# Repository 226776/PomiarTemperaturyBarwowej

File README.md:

# Pomiar Temperatury Barwowej
Repozytorium zawiera wszystkie niezbędne elementy projektu, najważniejsze z nich wymieniono poniżej:
- Katalog Hardware:
	- projekt płytki wykonany w środowisku eagle 
	- pining 
- Katalog pdf:
	- pdf płytką w skali 1:1  
	- pdf zawierający schemat układu akwizycji danych
- Katalog Scripts: 
	- skrypt wyliczający model
	- skrypt obsługujący pomiar temperatury barwowej
- Katalog MCU_Software:
	- pliki oprogramowania mikrokontrolera w tym plik main 
- Katalog Measurements 
	- pomiary źródeł światła
	- skrypty jupyter notebook

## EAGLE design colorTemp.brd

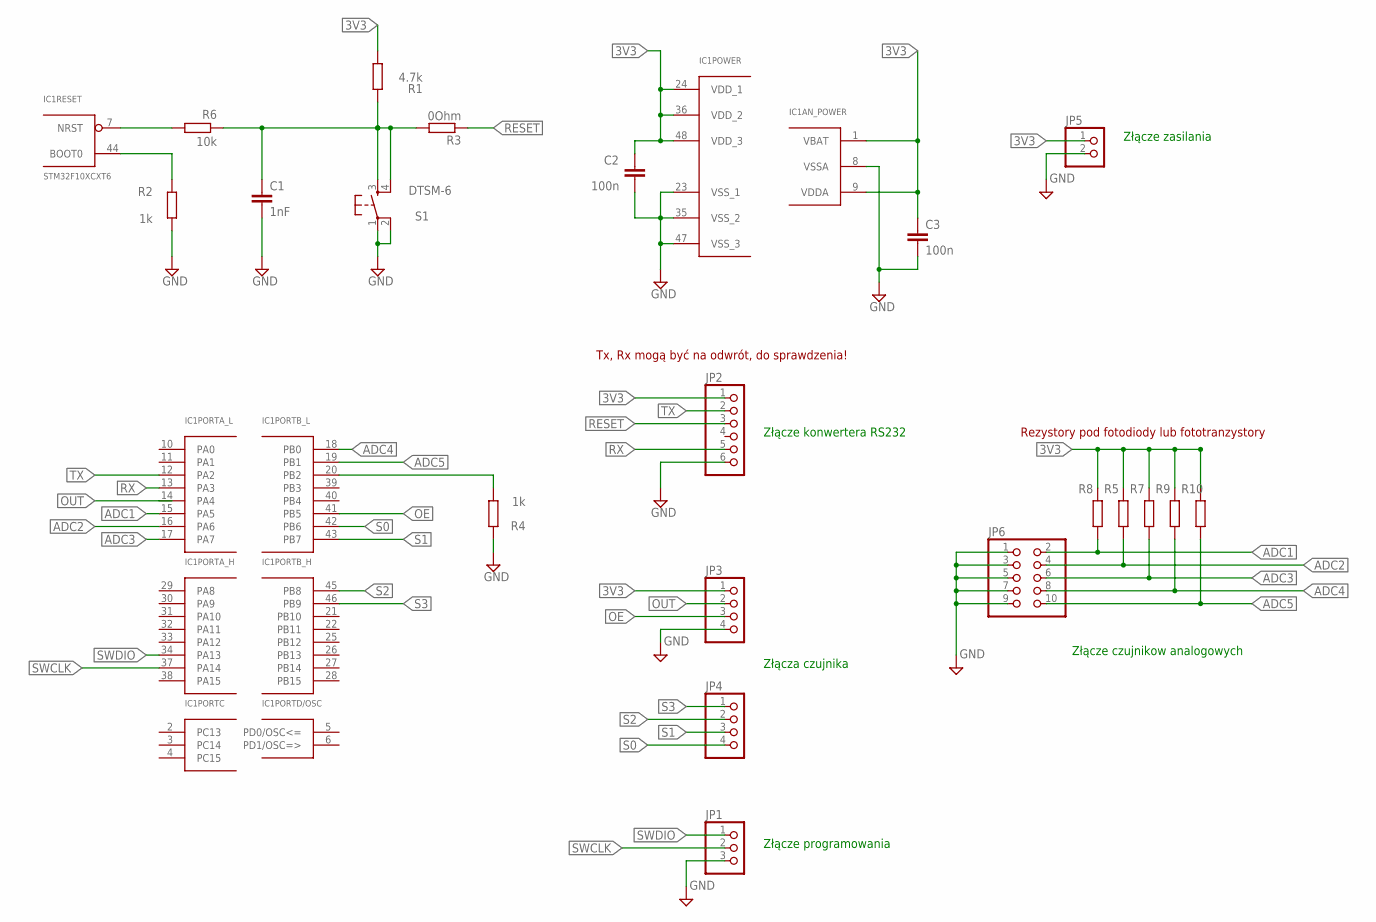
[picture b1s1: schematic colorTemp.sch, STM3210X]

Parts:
C1: 1nF; C0402
C2, C3: 100n; C0402
IC1: STM32F10XCXT6; TQFP48
JP1: PINHD-1X3; 1X03
JP2: PINHD-1X6/90; 1X06/90
JP3, JP4: PINHD-1X4; 1X04
JP5: PINHD-1X2; 1X02
JP6: PINHD-2X5; 2X05
R1: 4.7k; R0402
R2, R4: 1k; R0402
R3: 0Ohm; R0402
R5, R7, R8, R9, R10: R-EU_R0402; R0402
R6: 10k; R0402
S1: DTSM-6

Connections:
3V3: C2.1, C3.1, IC1.1 (VBAT), IC1.9 (VDDA), IC1.24 (VDD_1), IC1.36 (VDD_2), IC1.48 (VDD_3), JP2.1, JP3.1, JP5.1, R1.2, R5.1, R7.1, R8.1, R9.1, R10.1
ADC1: IC1.15 (PA5), JP6.2, R8.2
ADC2: IC1.16 (PA6), JP6.4, R5.2
ADC3: IC1.17 (PA7), JP6.6, R7.2
ADC4: IC1.18 (PB0), JP6.8, R9.2
ADC5: IC1.19 (PB1), JP6.10, R10.2
GND: C1.2, C2.2, C3.2, IC1.8 (VSSA), IC1.23 (VSS_1), IC1.35 (VSS_2), IC1.47 (VSS_3), JP1.3, JP2.6, JP3.4, JP5.2, JP6.1, JP6.3, JP6.5, JP6.7, JP6.9, R2.1, R4.1, S1.1, S1.2
unnamed: IC1.44 (BOOT0), R2.2
unnamed: IC1.20 (PB2), R4.2
unnamed: IC1.7 (NRST), R6.2
unnamed: C1.1, R1.1, R3.2, R6.1, S1.3, S1.4
OE: IC1.41 (PB5), JP3.3
OUT: IC1.14 (PA4), JP3.2
RESET: JP2.3, R3.1
RX: IC1.13 (PA3), JP2.5
S0: IC1.42 (PB6), JP4.4
S1: IC1.43 (PB7), JP4.3
S2: IC1.45 (PB8), JP4.2
S3: IC1.46 (PB9), JP4.1
SWCLK: IC1.37 (PA14), JP1.2
SWDIO: IC1.34 (PA13), JP1.1
TX: IC1.12 (PA2), JP2.2

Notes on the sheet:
Tx, Rx mogą być na odwrót, do sprawdzenia!
Złącze konwertera RS232
Złącza czujnika
Złącze programowania
Złącze zasilania
Złącze czujnikow analogowych
Rezystory pod fotodiody lub fototranzystory

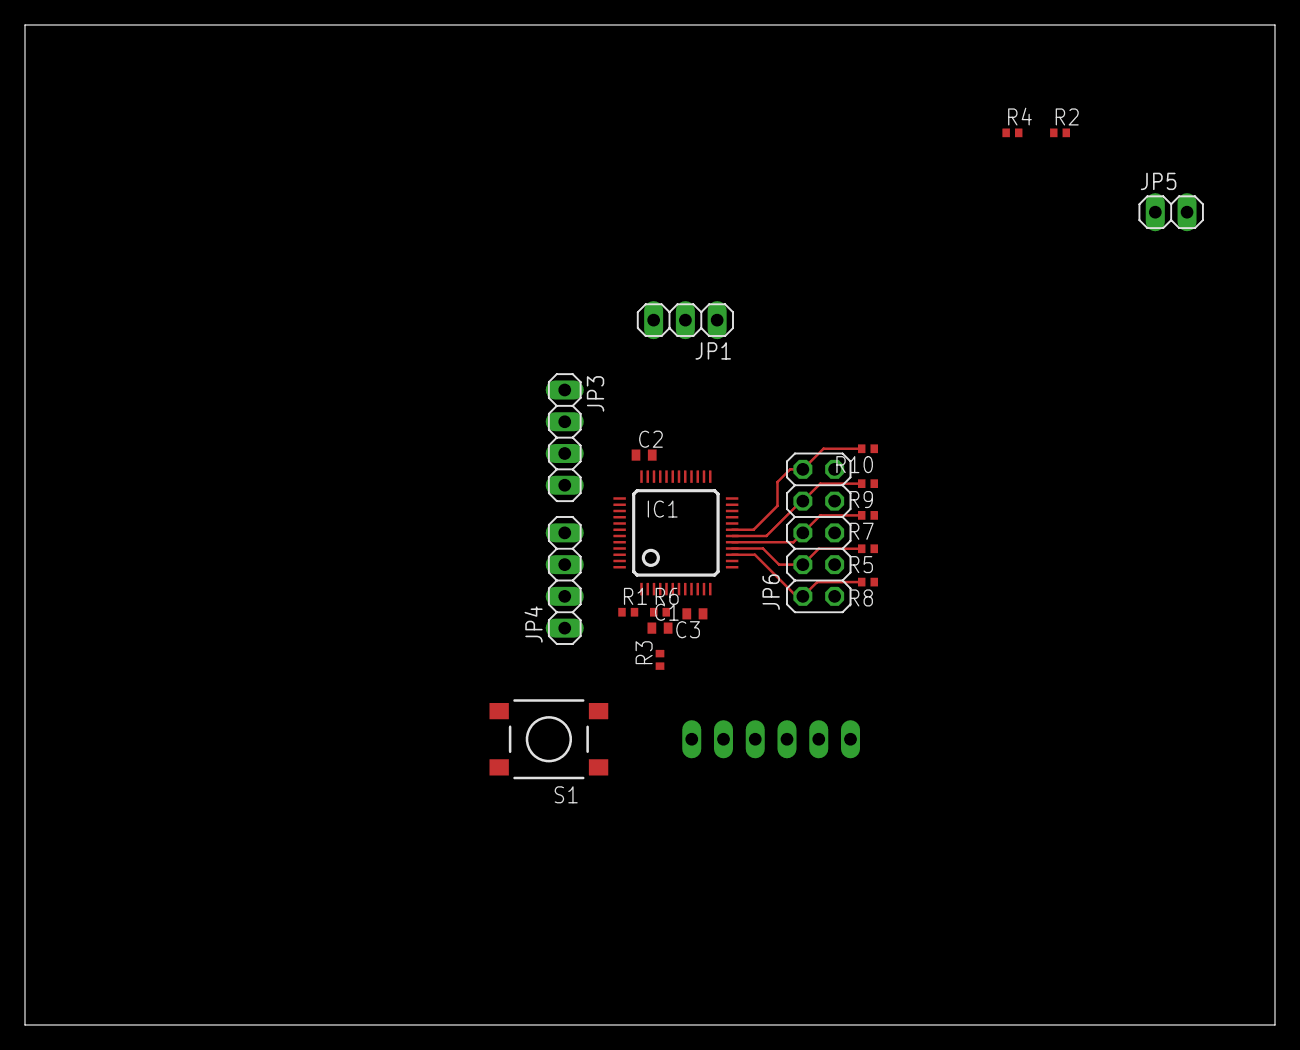
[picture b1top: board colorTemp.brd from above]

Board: 2 copper layers, 100.0 x 80.0 mm, 21 parts (1 on the bottom side), 22 nets.

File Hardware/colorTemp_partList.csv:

"Qty";"Value";"Device";"Package";"Parts";"Description";"SPICEPREFIX";
"1";"";"PINHD-1X2";"1X02";"JP5";"PIN HEADER";"";
"1";"";"PINHD-1X3";"1X03";"JP1";"PIN HEADER";"";
"2";"";"PINHD-1X4";"1X04";"JP3, JP4";"PIN HEADER";"";
"1";"";"PINHD-1X6/90";"1X06/90";"JP2";"PIN HEADER";"";
"1";"";"PINHD-2X5";"2X05";"JP6";"PIN HEADER";"";
"5";"";"R-EU_R0402";"R0402";"R5, R7, R8, R9, R10";"RESISTOR, European symbol";"R";
"1";"0Ohm";"R-EU_R0402";"R0402";"R3";"RESISTOR, European symbol";"R";
"2";"100n";"C-EUC0402";"C0402";"C2, C3";"CAPACITOR, European symbol";"C";
"1";"10k";"R-EU_R0402";"R0402";"R6";"RESISTOR, European symbol";"R";
"2";"1k";"R-EU_R0402";"R0402";"R2, R4";"RESISTOR, European symbol";"R";
"1";"1nF";"C-EUC0402";"C0402";"C1";"CAPACITOR, European symbol";"C";
"1";"4.7k";"R-EU_R0402";"R0402";"R1";"RESISTOR, European symbol";"R";
"1";"DTSM-6";"DTSM-6";"DTSM-6";"S1";"";"";
"1";"STM32F10XCXT6";"STM32F10XCXT6";"TQFP48";"IC1";"ST STM32F101/103 48pin LQFP";"";

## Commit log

2020-03-30 Pinning
2020-03-30 Cleanup
2020-04-05 Power supply schematic
2020-04-05 Schematic STM3210X section
2020-04-05 TCS3200 datasheet add
2020-04-05 Schematic pdf
2020-04-05 Supply change
2020-04-05 Schematic Update
2020-04-18 Board in progress
2020-04-18 Board update
2020-05-17 Images Upload
2020-05-17 Added new comments to the main.c file
2020-05-17 Added new comments in main.c file
2020-05-17 Images Rename
2020-05-18 Project CleanUp
2020-05-31 mesuing patterns
2020-05-31 Algorytm programu MCU
2020-05-31 Block Diagram add
2020-06-02 Measure via serial python script in progress
2020-06-07 BoardView.png upload
2020-06-07 Creating model, measurements
2020-06-07 Part list
2020-06-07 cleanup2
2020-06-07 Images Update
2020-06-07 Board 1:1 pdf
2020-06-07 README update
